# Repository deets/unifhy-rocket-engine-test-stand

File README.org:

* UNIFHY - universeller Prüfstand für Feststoff- und Hybridmotoren

Ziel dieses Projektes ist die Entwicklung eines preiswerten
Prüfstandes mit einem Preis von maximal 500 EUR.

Der Prüfstand besteht aus drei Modulen:

 - Modul 1: einem aus ITEM Prüfbalken bestehenden mechanischen Aufbau.
 - Modul 2: einer Prüfbox zur Datenaufnahme, Speicherung, Übermittlung und
   gegebenenfalls Fernsteuerung.
 - Modul 3: einer Software zur Konfiguration, Datenerfassung und Auswertung von Modul 2.

Hier die [[file:doc/Pruefstand_UNIFHY.pdf][Anforderungen erhoben am 22.02.2020]].

** Modul 1 - Teststand

Ein Aufbau des Testands von Andreas:

[[./doc/Teststand-Totale.jpg]]

[[./doc/Hybrid-Haengend.jpg]]

[[./doc/Test-mit-laufendem-Motor.jpg]]

** Modul 2 - Firmware

*** ADS1256 Breakout Board

Pin out of the breakout board as seen from top with control interface
to the left:

|-----+----------+---------|
| Pin | Function | P2 Eval |
|-----+----------+---------|
|   1 | PDWN     |      21 |
|   2 | CS_      |      20 |
|   3 | DRDY     |      19 |
|   4 | DOUT     |      17 |
|   5 | DIN      |      18 |
|   6 | SCLK     |      16 |
|   7 | GND      |     GND |
|   8 | 5V       |     EXT |
|-----+----------+---------|

#+attr_html: :width 400 px
[[file:doc/ads1256-breakout.jpg]]

** GIT Konfiguration

Wir arbeiten mit einem [[https://medium.com/singlestone/a-git-workflow-using-rebase-1b1210de83e5][rebase]] basierten GIT workflow. Dazu ist es
hilfreich eine Reihe von Einstellungen vorzunehmen. Die folgenden
Kommandos werden in einer Shell eingegeben, und man muss sich in
der Arbeitskopie befinden:

#+begin_src bash
git config pull.rebase true
#+end_src

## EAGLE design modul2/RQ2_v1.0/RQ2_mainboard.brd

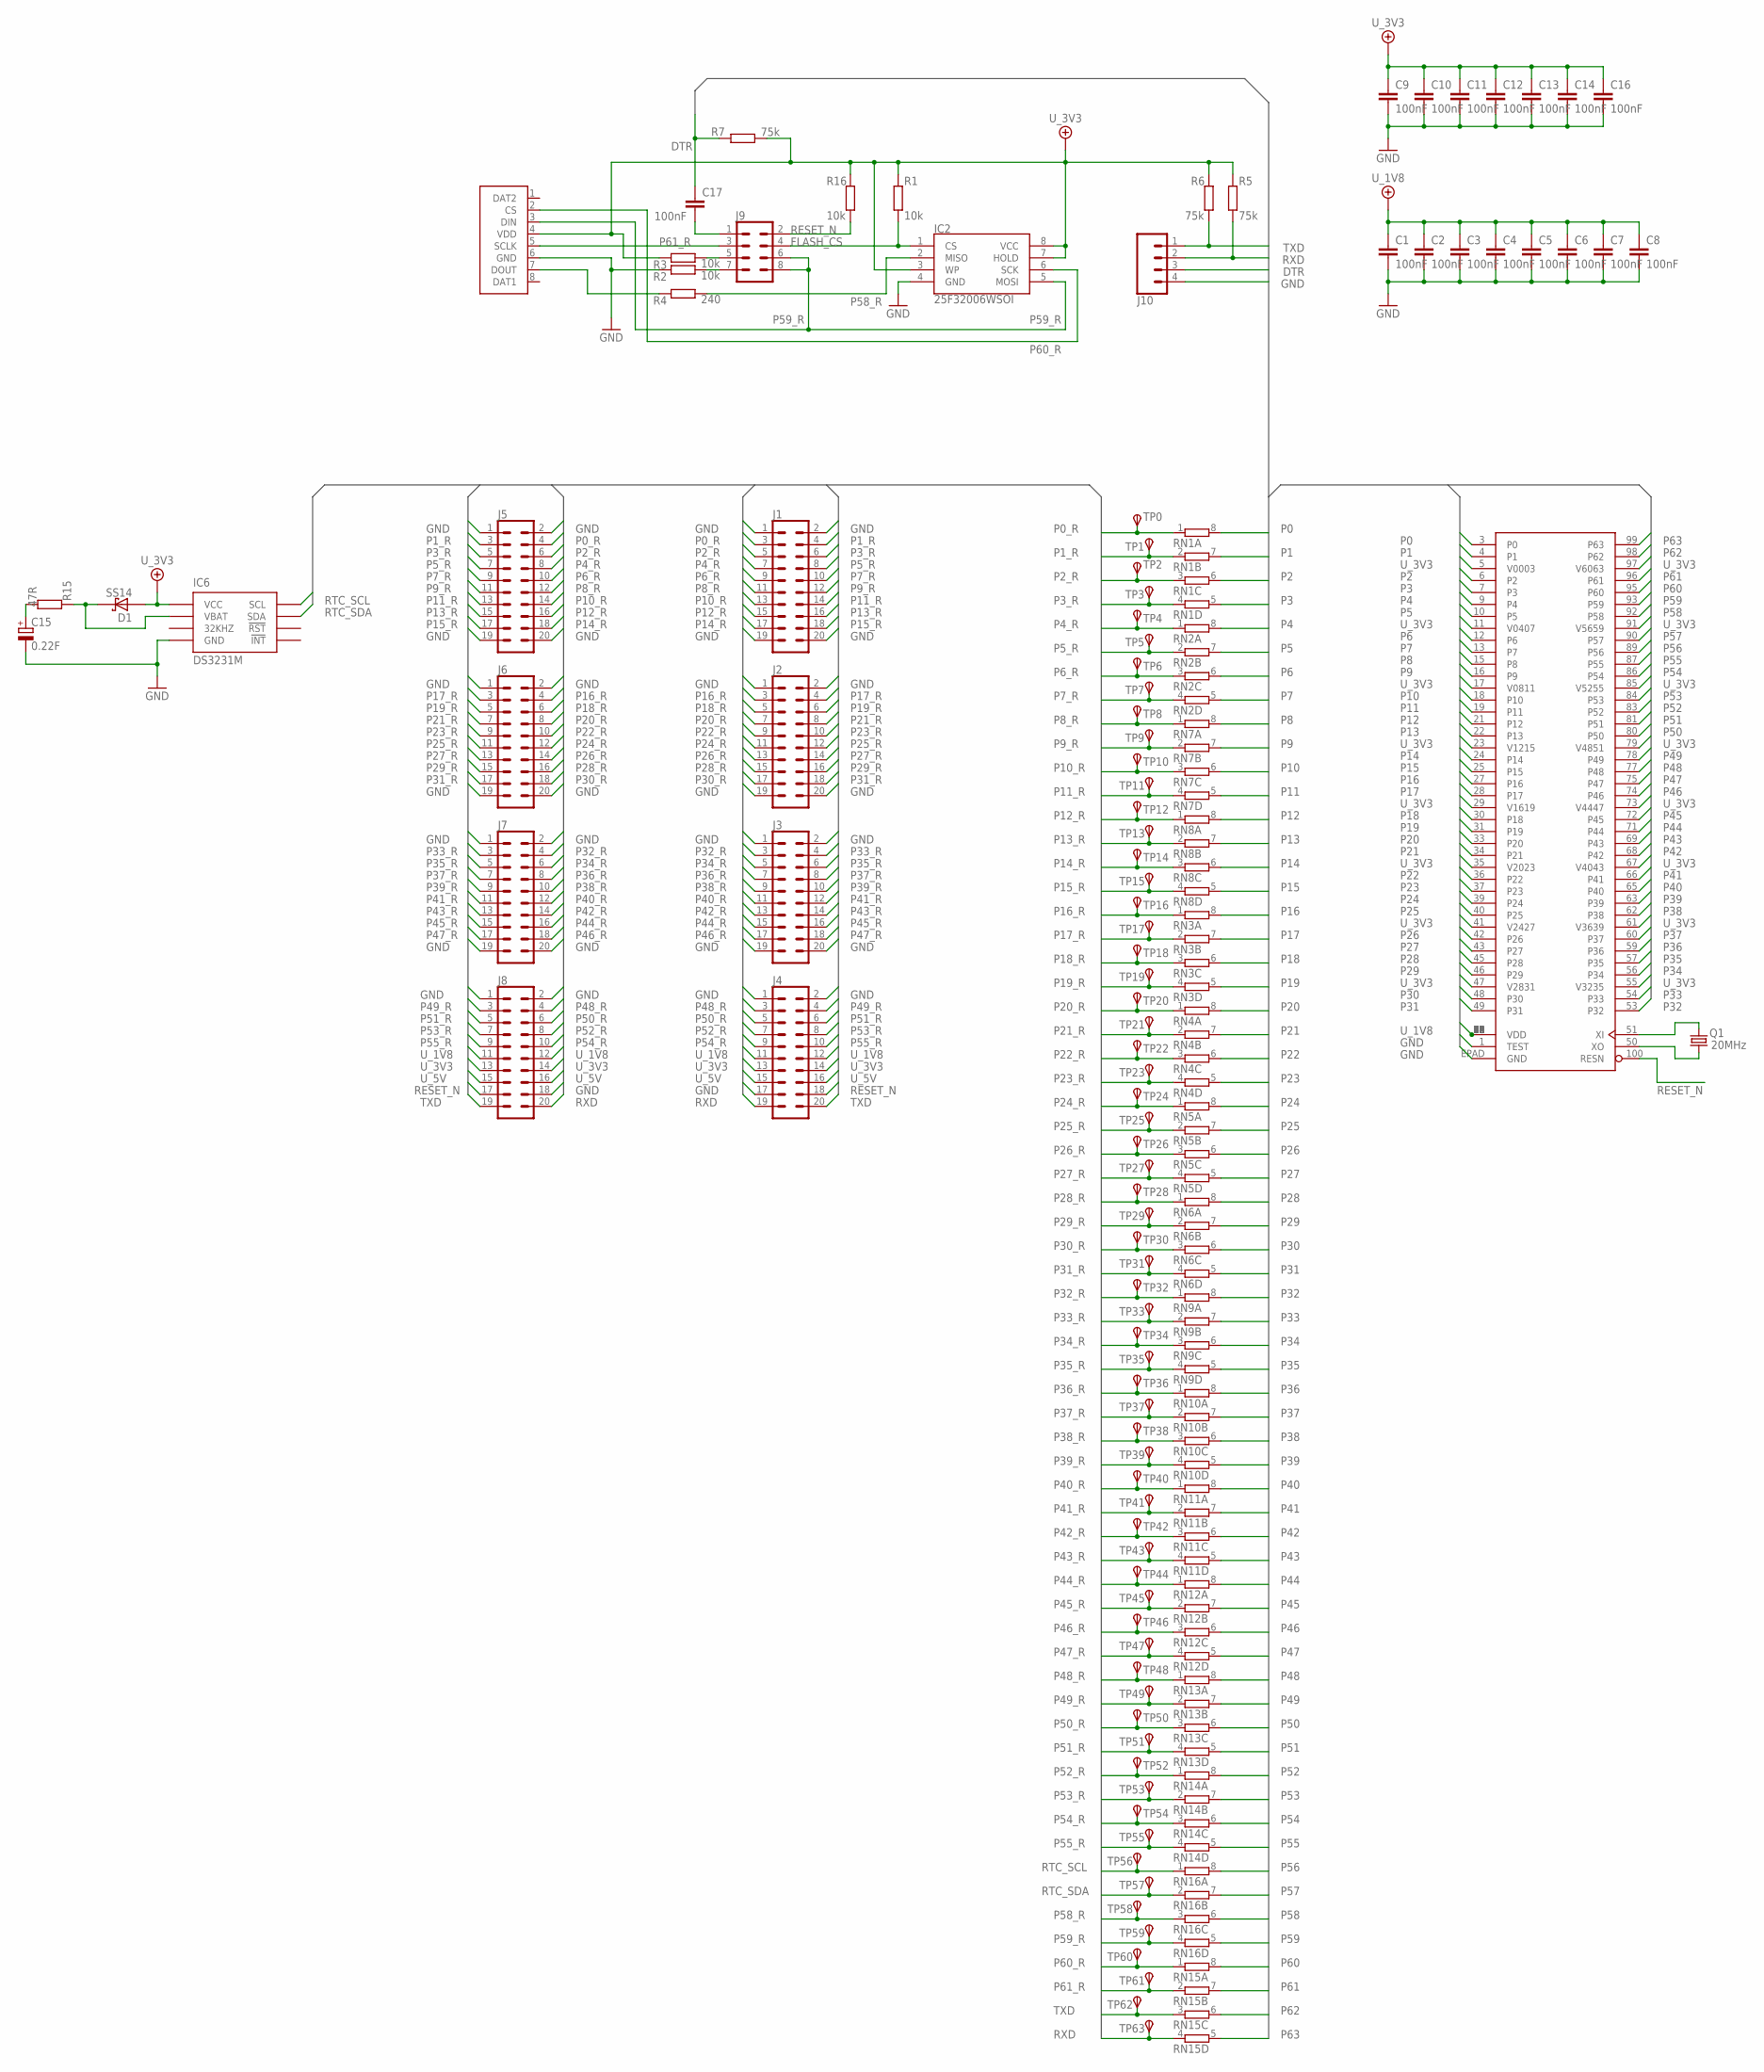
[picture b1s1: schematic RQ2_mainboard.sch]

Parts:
C1, C2, C3, C4, C5, C6, C7, C8, C9, C10, C11, C12, C13, C14, C16, C17: 100nF; C0805
C15: 0.22F; DHL_21.5
D1: SS14; SMA_403D
IC1: P2X8C4M64P; TQFP100
IC2: 25F32006WSOI; SO08-EIAJ
IC6: DS3231M; SO-8
J1, J2, J3, J4, J5, J6, J7, J8: CONN_10X2SMT; 2X10_SMT
J9: CONN_04X2; 2X4
J10: CONN_04; 1X04
Q1: 20MHz; CRYSTAL-SMD-5X3.2-2PAD
R1, R2, R3, R16: 10k; R0603
R4: 240; R0603
R5, R6, R7: 75k; R0603
R15: 47R; R0603
RN1, RN2, RN3, RN4, RN5, RN6, RN7, RN8, RN9, RN10, RN11, RN12, RN13, RN14, RN15, RN16: 4R-N0603-ARV; 0603-ARV
TP0, TP1, TP2, TP3, TP4, TP5, TP6, TP7, TP8, TP9, TP10, TP11, TP12, TP13, TP14, TP15, TP16, TP17, TP18, TP19, TP20, TP21, TP22, TP23, TP24, TP25, TP26, TP27, TP28, TP29, TP30, TP31, TP32, TP33, TP34, TP35, TP36, TP37, TP38, TP39, TP40, TP41, TP42, TP43, TP44, TP45, TP46, TP47, TP48, TP49, TP50, TP51, TP52, TP53, TP54, TP55, TP56, TP57, TP58, TP59, TP60, TP61, TP62, TP63: TPSB1,27; B1,27
X1: MICRO_SD_CONNECTORMOLEX_HINGE; MICRO_SD

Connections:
DTR: C17.1, J10.3, R7.2
DTR_C: C17.2, J9.1
FLASH_CS: IC2.1 (CS), J9.4, R1.1
GND: C1.2, C2.2, C3.2, C4.2, C5.2, C6.2, C7.2, C8.2, C9.2, C10.2, C11.2, C12.2, C13.2, C14.2, C15.-, C16.2, IC1.1 (TEST), IC1.EPAD (GND), IC2.4 (GND), IC6.5 (GND), J1.1, J1.2, J1.19, J1.20, J2.1, J2.2, J2.19, J2.20, J3.1, J3.2, J3.19, J3.20, J4.1, J4.2, J4.17, J5.1, J5.2, J5.19, J5.20, J6.1, J6.2, J6.19, J6.20, J7.1, J7.2, J7.19, J7.20, J8.1, J8.2, J8.18, J10.4, R2.2, X1.6 (GND)
unnamed: J9.7, R2.1
unnamed: J9.5, R3.1
P0: IC1.3 (P0), RN1.8 (2)
P0_R: J1.3, J5.4, RN1.1, TP0.TP
P1: IC1.4 (P1), RN1.7 (2)
P1_R: J1.4, J5.3, RN1.2 (1), TP1.TP
P2: IC1.6 (P2), RN1.6 (2)
P2_R: J1.5, J5.6, RN1.3 (1), TP2.TP
P3: IC1.7 (P3), RN1.5 (2)
P3_R: J1.6, J5.5, RN1.4 (1), TP3.TP
P4: IC1.9 (P4), RN2.8 (2)
P4_R: J1.7, J5.8, RN2.1, TP4.TP
P5: IC1.10 (P5), RN2.7 (2)
P5_R: J1.8, J5.7, RN2.2 (1), TP5.TP
P6: IC1.12 (P6), RN2.6 (2)
P6_R: J1.9, J5.10, RN2.3 (1), TP6.TP
P7: IC1.13 (P7), RN2.5 (2)
P7_R: J1.10, J5.9, RN2.4 (1), TP7.TP
P8: IC1.15 (P8), RN7.8 (2)
P8_R: J1.11, J5.12, RN7.1, TP8.TP
P9: IC1.16 (P9), RN7.7 (2)
P9_R: J1.12, J5.11, RN7.2 (1), TP9.TP
P10: IC1.18 (P10), RN7.6 (2)
P10_R: J1.13, J5.14, RN7.3 (1), TP10.TP
P11: IC1.19 (P11), RN7.5 (2)
P11_R: J1.14, J5.13, RN7.4 (1), TP11.TP
P12: IC1.21 (P12), RN8.8 (2)
P12_R: J1.15, J5.16, RN8.1, TP12.TP
P13: IC1.22 (P13), RN8.7 (2)
P13_R: J1.16, J5.15, RN8.2 (1), TP13.TP
P14: IC1.24 (P14), RN8.6 (2)
P14_R: J1.17, J5.18, RN8.3 (1), TP14.TP
P15: IC1.25 (P15), RN8.5 (2)
P15_R: J1.18, J5.17, RN8.4 (1), TP15.TP
P16: IC1.27 (P16), RN3.8 (2)
P16_R: J2.3, J6.4, RN3.1, TP16.TP
P17: IC1.28 (P17), RN3.7 (2)
P17_R: J2.4, J6.3, RN3.2 (1), TP17.TP
P18: IC1.30 (P18), RN3.6 (2)
P18_R: J2.5, J6.6, RN3.3 (1), TP18.TP
P19: IC1.31 (P19), RN3.5 (2)
P19_R: J2.6, J6.5, RN3.4 (1), TP19.TP
P20: IC1.33 (P20), RN4.8 (2)
P20_R: J2.7, J6.8, RN4.1, TP20.TP
P21: IC1.34 (P21), RN4.7 (2)
P21_R: J2.8, J6.7, RN4.2 (1), TP21.TP
P22: IC1.36 (P22), RN4.6 (2)
P22_R: J2.9, J6.10, RN4.3 (1), TP22.TP
P23: IC1.37 (P23), RN4.5 (2)
P23_R: J2.10, J6.9, RN4.4 (1), TP23.TP
P24: IC1.39 (P24), RN5.8 (2)
P24_R: J2.11, J6.12, RN5.1, TP24.TP
P25: IC1.40 (P25), RN5.7 (2)
P25_R: J2.12, J6.11, RN5.2 (1), TP25.TP
P26: IC1.42 (P26), RN5.6 (2)
P26_R: J2.13, J6.14, RN5.3 (1), TP26.TP
P27: IC1.43 (P27), RN5.5 (2)
P27_R: J2.14, J6.13, RN5.4 (1), TP27.TP
P28: IC1.45 (P28), RN6.8 (2)
P28_R: J2.15, J6.16, RN6.1, TP28.TP
P29: IC1.46 (P29), RN6.7 (2)
P29_R: J2.16, J6.15, RN6.2 (1), TP29.TP
P30: IC1.48 (P30), RN6.6 (2)
P30_R: J2.17, J6.18, RN6.3 (1), TP30.TP
P31: IC1.49 (P31), RN6.5 (2)
P31_R: J2.18, J6.17, RN6.4 (1), TP31.TP
P32: IC1.53 (P32), RN9.8 (2)
P32_R: J3.3, J7.4, RN9.1, TP32.TP
P33: IC1.54 (P33), RN9.7 (2)
P33_R: J3.4, J7.3, RN9.2 (1), TP33.TP
P34: IC1.56 (P34), RN9.6 (2)
P34_R: J3.5, J7.6, RN9.3 (1), TP34.TP
P35: IC1.57 (P35), RN9.5 (2)
P35_R: J3.6, J7.5, RN9.4 (1), TP35.TP
P36: IC1.59 (P36), RN10.8 (2)
P36_R: J3.7, J7.8, RN10.1, TP36.TP
P37: IC1.60 (P37), RN10.7 (2)
P37_R: J3.8, J7.7, RN10.2 (1), TP37.TP
P38: IC1.62 (P38), RN10.6 (2)
P38_R: J3.9, J7.10, RN10.3 (1), TP38.TP
P39: IC1.63 (P39), RN10.5 (2)
P39_R: J3.10, J7.9, RN10.4 (1), TP39.TP
P40: IC1.65 (P40), RN11.8 (2)
P40_R: J3.11, J7.12, RN11.1, TP40.TP
P41: IC1.66 (P41), RN11.7 (2)
P41_R: J3.12, J7.11, RN11.2 (1), TP41.TP
P42: IC1.68 (P42), RN11.6 (2)
P42_R: J3.13, J7.14, RN11.3 (1), TP42.TP
P43: IC1.69 (P43), RN11.5 (2)
P43_R: J3.14, J7.13, RN11.4 (1), TP43.TP
P44: IC1.71 (P44), RN12.8 (2)
P44_R: J3.15, J7.16, RN12.1, TP44.TP
P45: IC1.72 (P45), RN12.7 (2)
P45_R: J3.16, J7.15, RN12.2 (1), TP45.TP
P46: IC1.74 (P46), RN12.6 (2)
P46_R: J3.17, J7.18, RN12.3 (1), TP46.TP
P47: IC1.75 (P47), RN12.5 (2)
P47_R: J3.18, J7.17, RN12.4 (1), TP47.TP
P48: IC1.77 (P48), RN13.8 (2)
P48_R: J4.3, J8.4, RN13.1, TP48.TP
P49: IC1.78 (P49), RN13.7 (2)
P49_R: J4.4, J8.3, RN13.2 (1), TP49.TP
P50: IC1.80 (P50), RN13.6 (2)
P50_R: J4.5, J8.6, RN13.3 (1), TP50.TP
P51: IC1.81 (P51), RN13.5 (2)
P51_R: J4.6, J8.5, RN13.4 (1), TP51.TP
P52: IC1.83 (P52), RN14.8 (2)
P52_R: J4.7, J8.8, RN14.1, TP52.TP
P53: IC1.84 (P53), RN14.7 (2)
P53_R: J4.8, J8.7, RN14.2 (1), TP53.TP
P54: IC1.86 (P54), RN14.6 (2)
P54_R: J4.9, J8.10, RN14.3 (1), TP54.TP
P55: IC1.87 (P55), RN14.5 (2)
P55_R: J4.10, J8.9, RN14.4 (1), TP55.TP
P56: IC1.89 (P56), RN16.8 (2)
P57: IC1.90 (P57), RN16.7 (2)
P58: IC1.92 (P58), RN16.6 (2)
P58_R: IC2.2 (MISO), R4.1, RN16.3 (1), TP58.TP
P59: IC1.93 (P59), RN16.5 (2)
P59_R: IC2.5 (MOSI), J9.6, J9.8, RN16.4 (1), TP59.TP, X1.3 (DIN)
P60: IC1.95 (P60), RN15.8 (2)
P60_R: IC2.6 (SCK), RN15.1, TP60.TP, X1.2 (CS)
P61: IC1.96 (P61), RN15.7 (2)
P61_R: J9.3, RN15.2 (1), TP61.TP, X1.5 (SCLK)
P62: IC1.98 (P62), RN15.6 (2)
P63: IC1.99 (P63), RN15.5 (2)
RESET_N: IC1.100 (RESN), J4.18, J8.17, J9.2, R16.1
RTC_SCL: IC6.8 (SCL), RN16.1, TP56.TP
RTC_SDA: IC6.7 (SDA), RN16.2 (1), TP57.TP
RXD: J4.19, J8.20, J10.2, R5.1, RN15.4 (1), TP63.TP
SD_DOUT: R4.2, X1.7 (DOUT)
TXD: J4.20, J8.19, J10.1, R6.1, RN15.3 (1), TP62.TP
U_1V8: C1.1, C2.1, C3.1, C4.1, C5.1, C6.1, C7.1, C8.1, IC1.2 (VDD), IC1.8 (VDD), IC1.14 (VDD), IC1.20 (VDD), IC1.26 (VDD), IC1.32 (VDD), IC1.38 (VDD), IC1.44 (VDD), IC1.52 (VDD), IC1.58 (VDD), IC1.64 (VDD), IC1.70 (VDD), IC1.76 (VDD), IC1.82 (VDD), IC1.88 (VDD), IC1.94 (VDD), J4.11, J4.12, J8.11, J8.12
U_3V3: C9.1, C10.1, C11.1, C12.1, C13.1, C14.1, C16.1, D1.A, IC1.5 (V0003), IC1.11 (V0407), IC1.17 (V0811), IC1.23 (V1215), IC1.29 (V1619), IC1.35 (V2023), IC1.41 (V2427), IC1.47 (V2831), IC1.55 (V3235), IC1.61 (V3639), IC1.67 (V4043), IC1.73 (V4447), IC1.79 (V4851), IC1.85 (V5255), IC1.91 (V5659), IC1.97 (V6063), IC2.3 (WP), IC2.7 (HOLD), IC2.8 (VCC), IC6.2 (VCC), J4.13, J4.14, J8.13, J8.14, R1.2, R3.2, R5.2, R6.2, R7.1, R16.2, X1.4 (VDD)
U_5V: J4.15, J4.16, J8.15, J8.16
VBAT: D1.C, IC6.6 (VBAT), R15.1
VCAP: C15.+, R15.2
XIN: IC1.51 (XI), Q1.P$2 (2)
XOUT: IC1.50 (XO), Q1.P$1 (1)

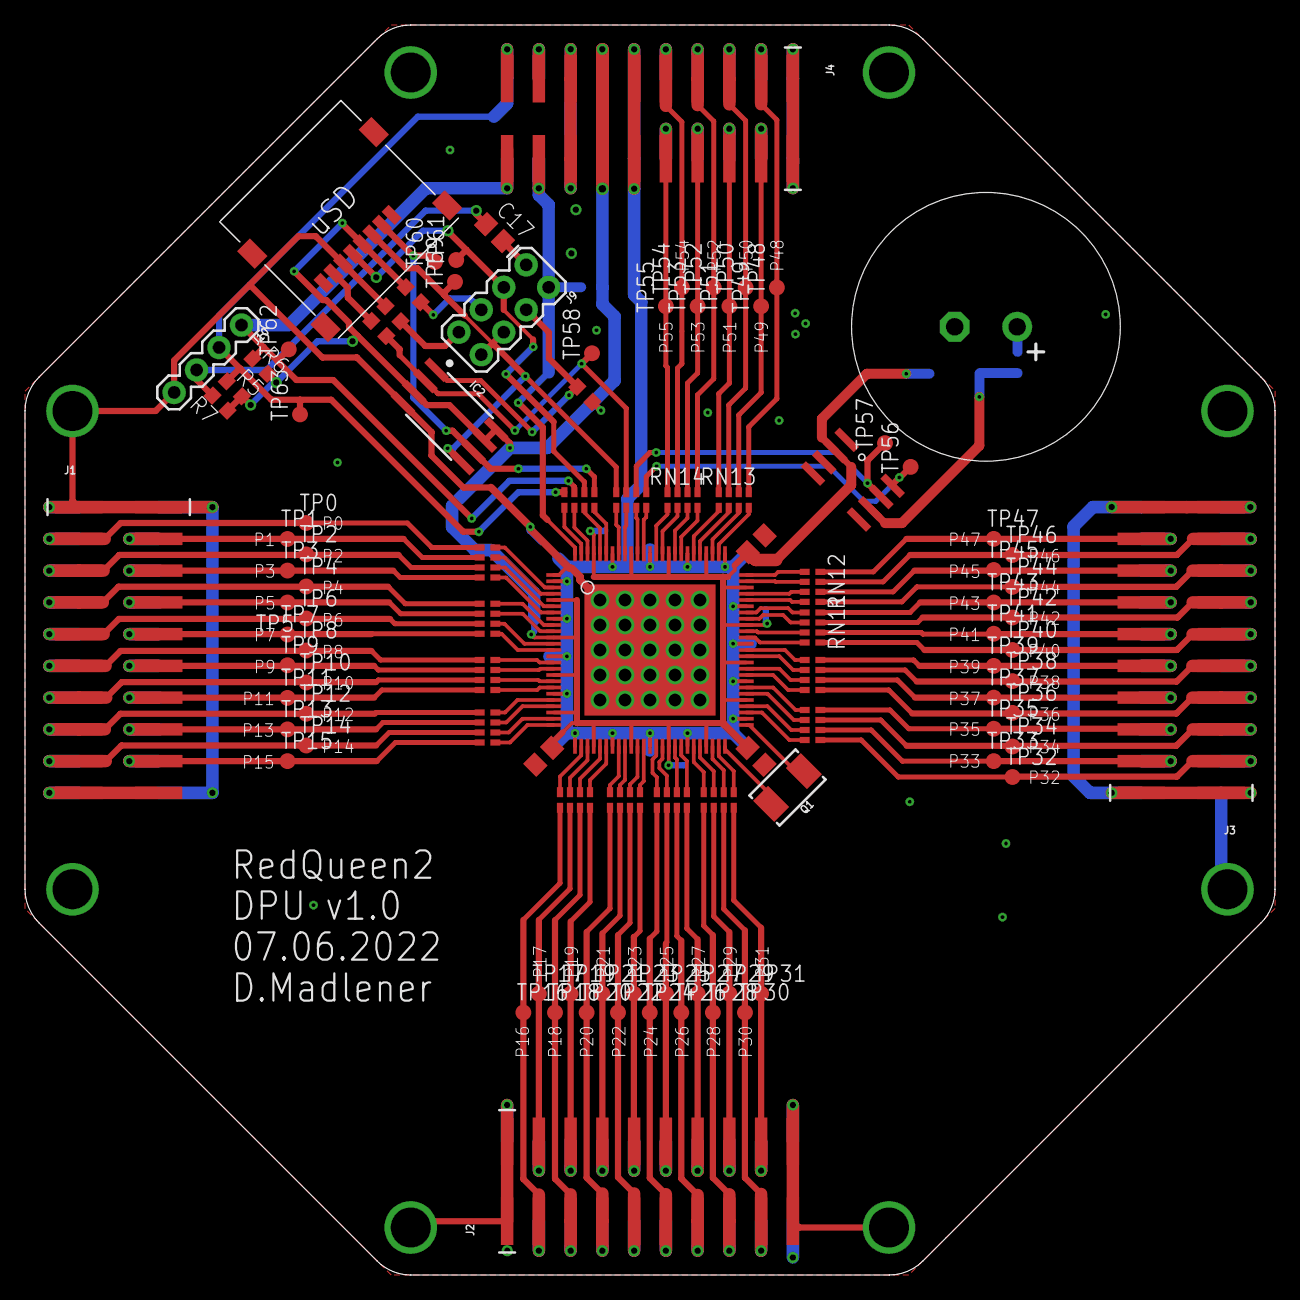
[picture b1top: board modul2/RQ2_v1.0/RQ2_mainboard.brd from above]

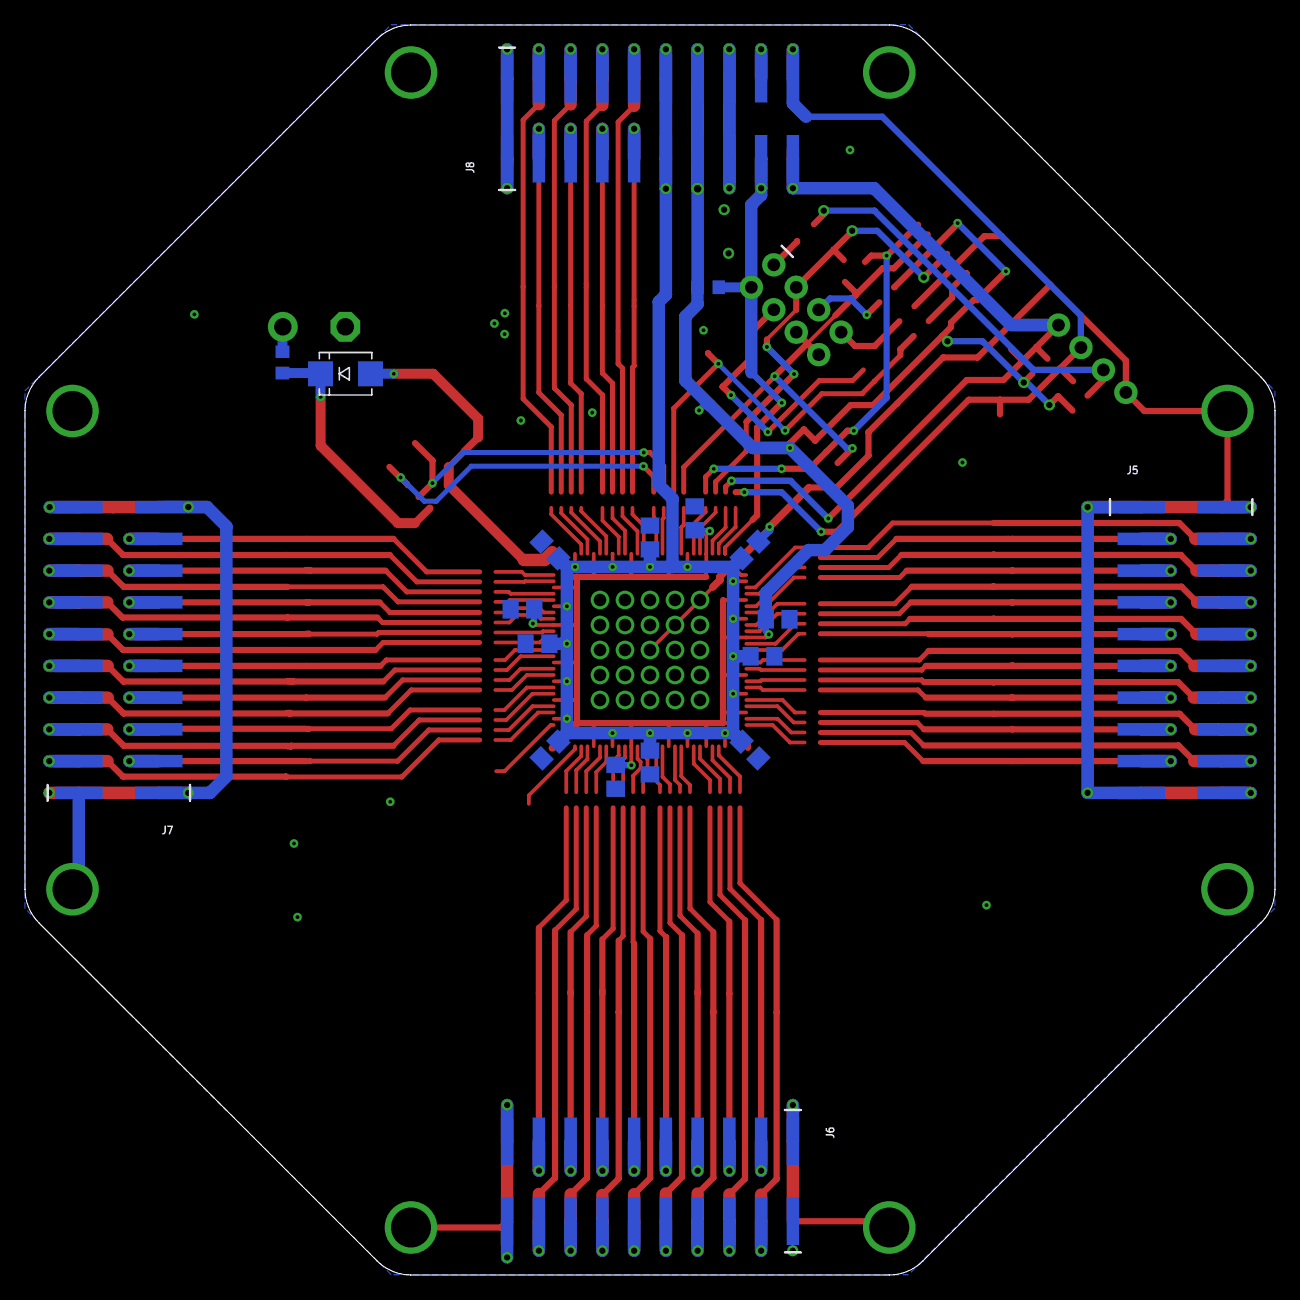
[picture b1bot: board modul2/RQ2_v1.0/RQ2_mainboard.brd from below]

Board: 2 copper layers, 100.0 x 100.0 mm, 122 parts (19 on the bottom side), 143 nets.

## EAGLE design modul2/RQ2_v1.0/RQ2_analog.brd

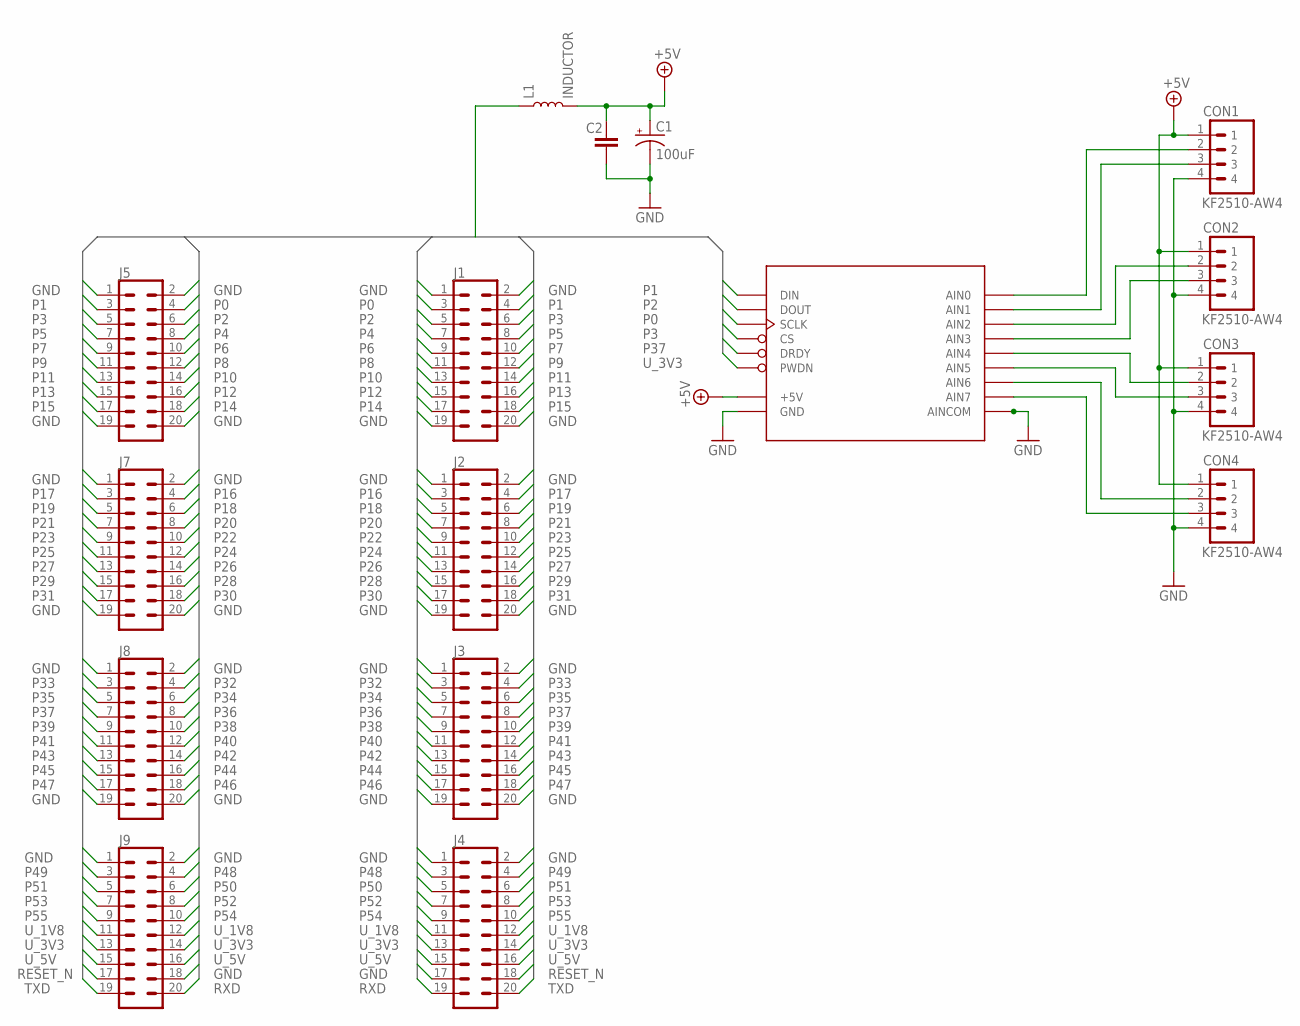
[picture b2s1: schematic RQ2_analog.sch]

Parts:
C1: 100uF; NIC_10X10.5_CAP
C2: 22uF; 1210
CON1, CON2, CON3, CON4: KF2510-AW4
J1, J2, J3, J4, J5, J7, J8, J9: CONN_10X2SMT; 2X10_SMT
L1: INDUCTOR; 1040
U$1: ADS1256_MODULE

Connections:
+5V: C1.+, C2.1, CON1.1, CON2.1, CON3.1, CON4.1, L1.2, U$1.+5V
GND: C1.-, C2.2, CON1.4, CON2.4, CON3.4, CON4.4, J1.1, J1.2, J1.19, J1.20, J2.1, J2.2, J2.19, J2.20, J3.1, J3.2, J3.19, J3.20, J4.1, J4.2, J4.17, J5.1, J5.2, J5.19, J5.20, J7.1, J7.2, J7.19, J7.20, J8.1, J8.2, J8.19, J8.20, J9.1, J9.2, J9.18, U$1.AINCOM0 (AINCOM), U$1.AINCOM1 (AINCOM), U$1.AINCOM2 (AINCOM), U$1.AINCOM3 (AINCOM), U$1.AINCOM4 (AINCOM), U$1.AINCOM5 (AINCOM), U$1.AINCOM6 (AINCOM), U$1.AINCOM7 (AINCOM), U$1.GND
unnamed: CON1.2, U$1.AIN0
unnamed: CON1.3, U$1.AIN1
unnamed: CON2.2, U$1.AIN2
unnamed: CON2.3, U$1.AIN3
unnamed: CON3.2, U$1.AIN4
unnamed: CON3.3, U$1.AIN5
unnamed: CON4.2, U$1.AIN6
unnamed: CON4.3, U$1.AIN7
P0: J1.3, J5.4, U$1.SCLK
P1: J1.4, J5.3, U$1.DIN
P2: J1.5, J5.6, U$1.DOUT
P3: J1.6, J5.5, U$1.CS
P4: J1.7, J5.8
P5: J1.8, J5.7
P6: J1.9, J5.10
P7: J1.10, J5.9
P8: J1.11, J5.12
P9: J1.12, J5.11
P10: J1.13, J5.14
P11: J1.14, J5.13
P12: J1.15, J5.16
P13: J1.16, J5.15
P14: J1.17, J5.18
P15: J1.18, J5.17
P16: J2.3, J7.4
P17: J2.4, J7.3
P18: J2.5, J7.6
P19: J2.6, J7.5
P20: J2.7, J7.8
P21: J2.8, J7.7
P22: J2.9, J7.10
P23: J2.10, J7.9
P24: J2.11, J7.12
P25: J2.12, J7.11
P26: J2.13, J7.14
P27: J2.14, J7.13
P28: J2.15, J7.16
P29: J2.16, J7.15
P30: J2.17, J7.18
P31: J2.18, J7.17
P32: J3.3, J8.4
P33: J3.4, J8.3
P34: J3.5, J8.6
P35: J3.6, J8.5
P36: J3.7, J8.8
P37: J3.8, J8.7, U$1.DRDY
P38: J3.9, J8.10
P39: J3.10, J8.9
P40: J3.11, J8.12
P41: J3.12, J8.11
P42: J3.13, J8.14
P43: J3.14, J8.13
P44: J3.15, J8.16
P45: J3.16, J8.15
P46: J3.17, J8.18
P47: J3.18, J8.17
P48: J4.3, J9.4
P49: J4.4, J9.3
P50: J4.5, J9.6
P51: J4.6, J9.5
P52: J4.7, J9.8
P53: J4.8, J9.7
P54: J4.9, J9.10
P55: J4.10, J9.9
RESET_N: J4.18, J9.17
RXD: J4.19, J9.20
TXD: J4.20, J9.19
U_1V8: J4.11, J4.12, J9.11, J9.12
U_3V3: J4.13, J4.14, J9.13, J9.14, U$1.PWDN
U_5V: J4.15, J4.16, J9.15, J9.16, L1.1

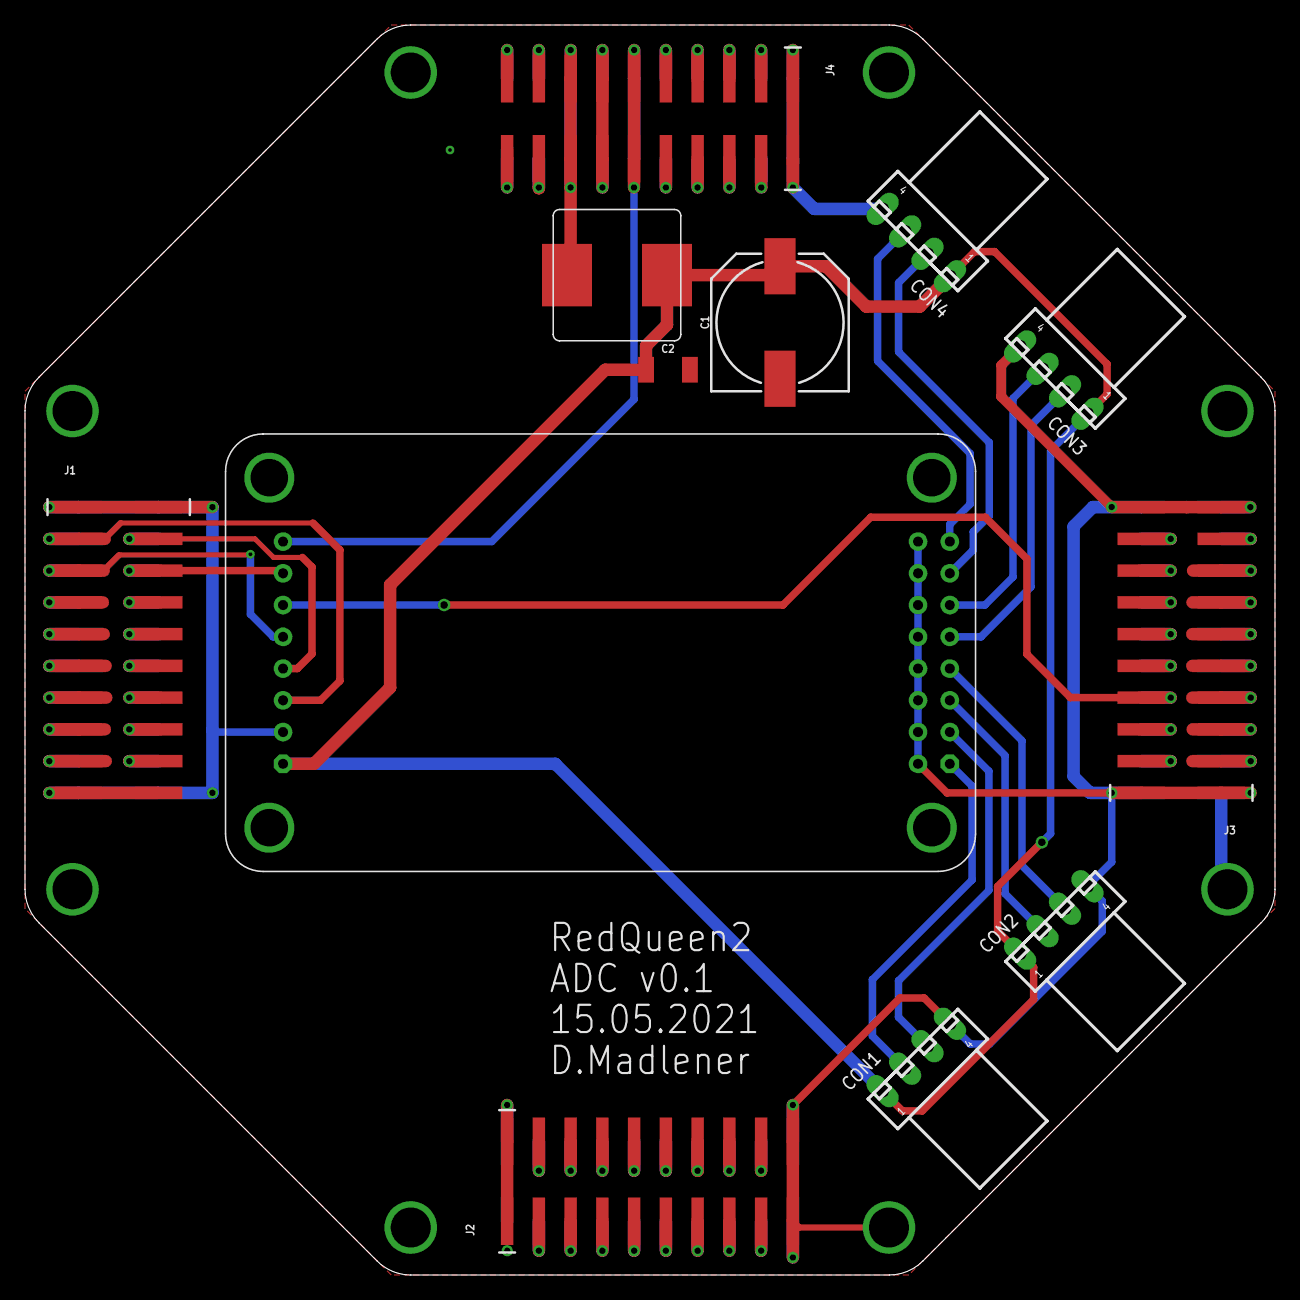
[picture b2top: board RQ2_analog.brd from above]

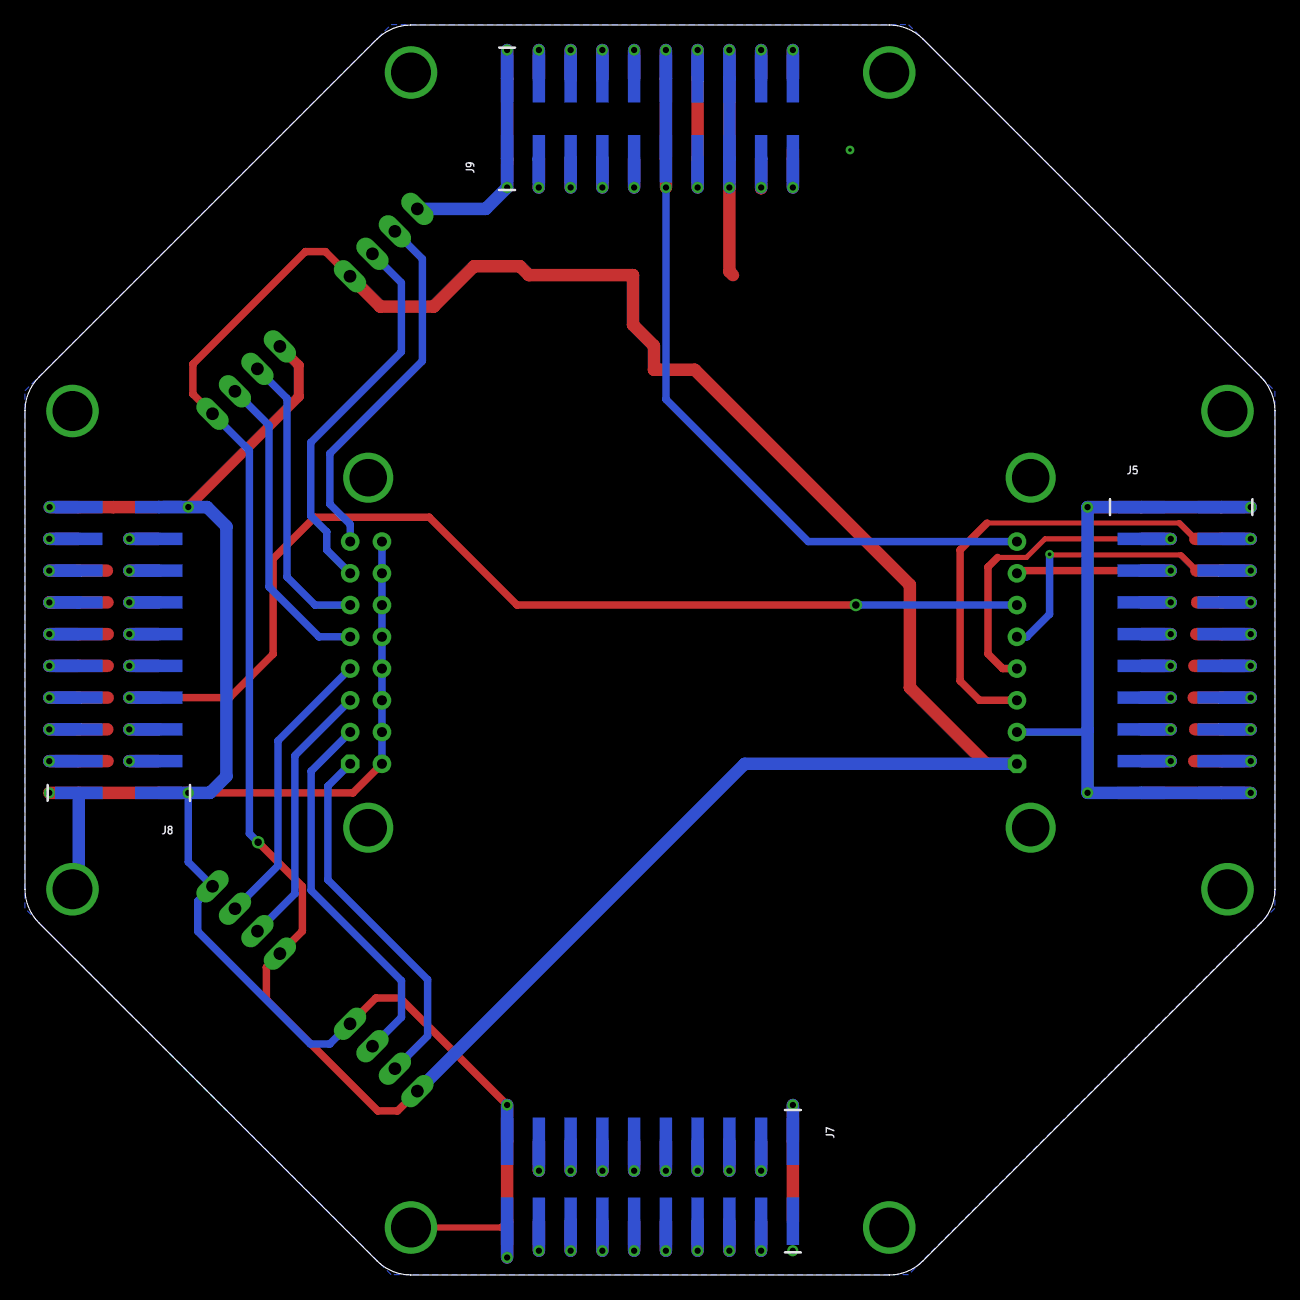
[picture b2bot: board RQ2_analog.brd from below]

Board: 2 copper layers, 100.0 x 100.0 mm, 16 parts (4 on the bottom side), 72 nets.

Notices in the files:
parts and their libraries:
SparkFun-Connectors: Licensing: Creative Commons ShareAlike 4.0 International - https://creativecommons.org/licenses/by-sa/4.0
FaBo-Sensor: Released under the Creative Commons Attribution-ShareAlike 4.0 License
https://creativecommons.org/licenses/by-sa/4.0
